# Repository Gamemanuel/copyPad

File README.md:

# copyPad
a macro pad for prgramers

# screenshot of overall hackpad

# A screenshot of my schematic

# A screenshot of my PCB

# BOM
* OLED screen
* encoder
* 4 headsetinserts
* 6 switches
* 6 Diodes
* 6 LEDS

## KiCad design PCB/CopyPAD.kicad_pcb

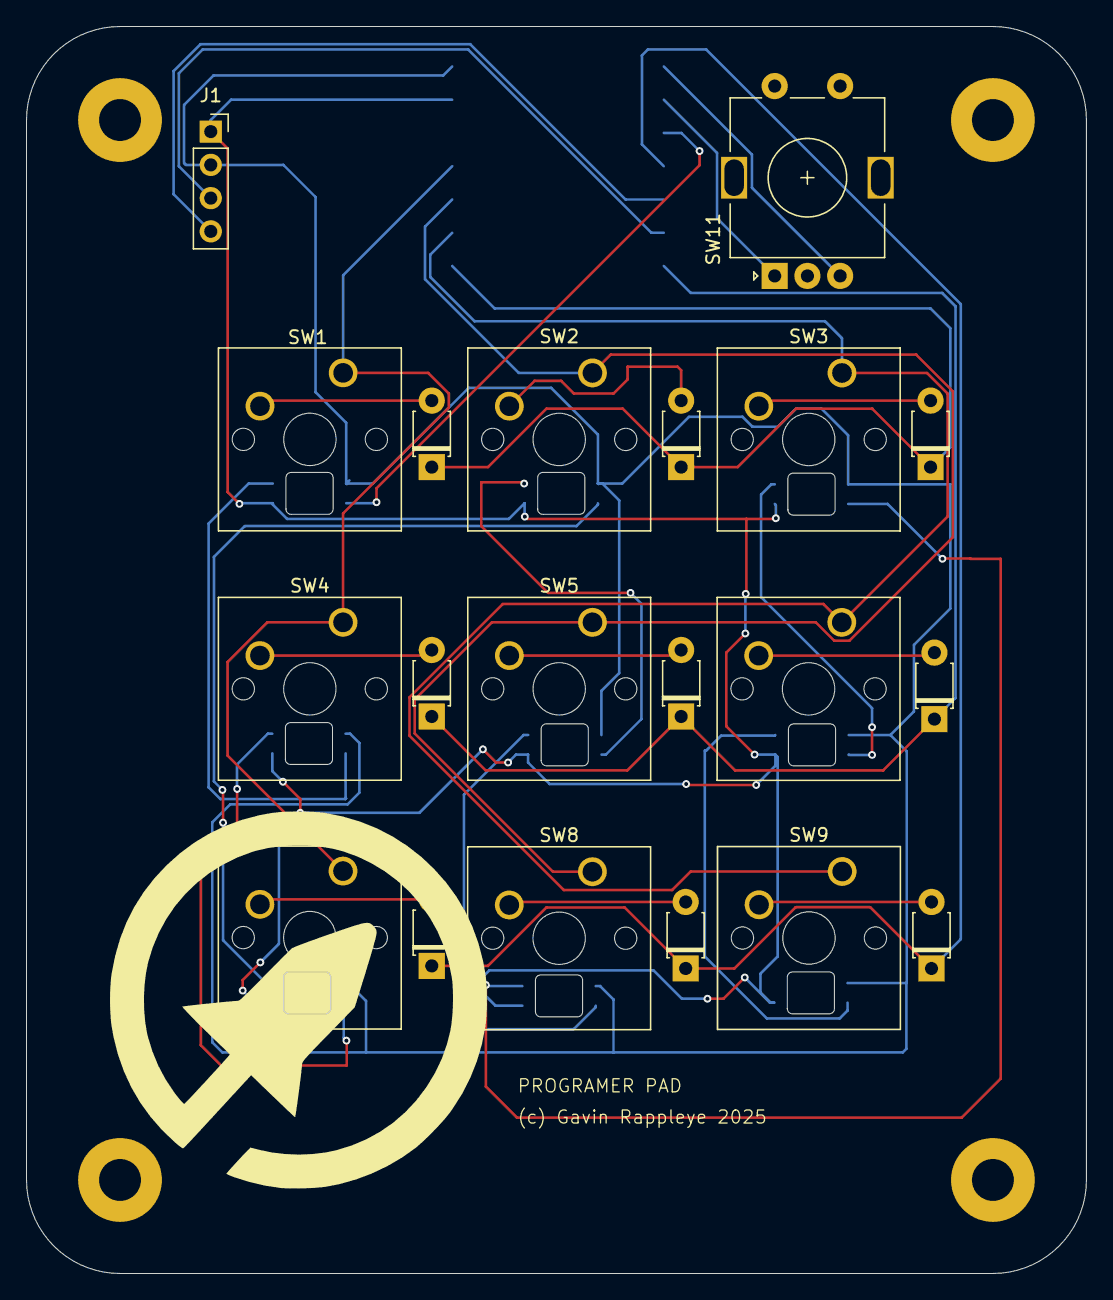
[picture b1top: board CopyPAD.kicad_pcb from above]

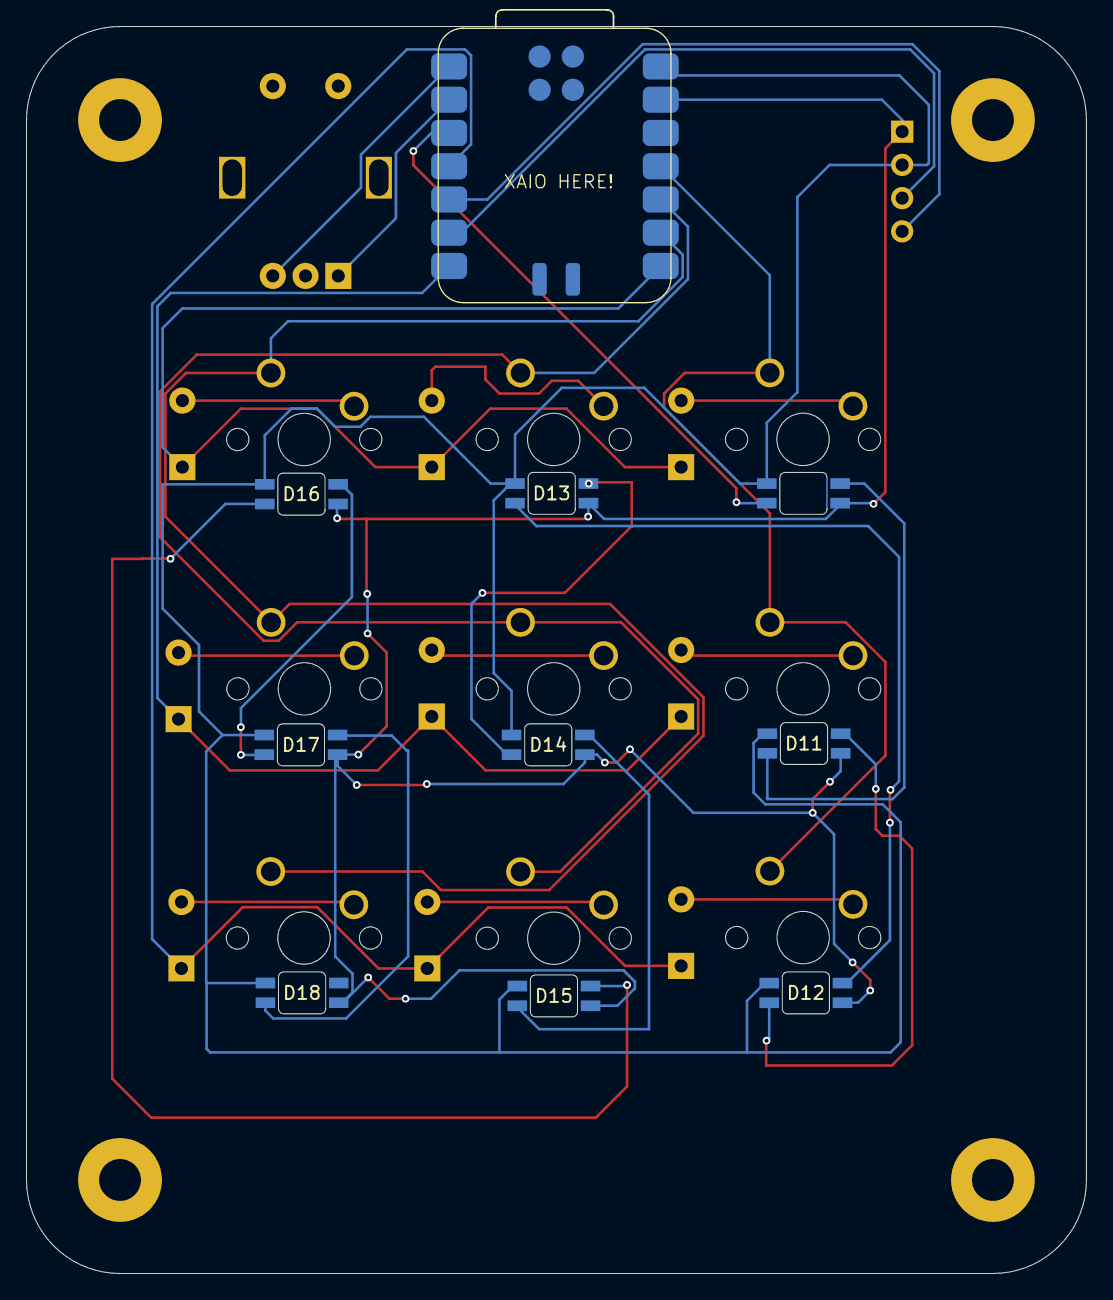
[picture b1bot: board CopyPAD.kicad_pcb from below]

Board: 2 copper layers, 81.0 x 95.2 mm, 34 parts (10 on the bottom side), 30 nets.

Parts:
D1, D11, D12, D13, D14, D15, D16, D17, D18: SK6812MINI; BAcklight
D2, D3, D4, D5, D6, D7, D8, D9, D10: D; D_T-1_P5.08mm_Horizontal
H1, H2, H3, H4: MountingHole; MountingHole_3.2mm_M3_Pad
J1: Conn_01x04_MountingPin; PinSocket_1x04_P2.54mm_Vertical
SW1, SW2, SW3, SW4, SW5, SW6, SW7, SW8, SW9: SW_Push_45deg; SW_Cherry_MX_1.00u_PCB
SW11: RotaryEncoder_Switch; RotaryEncoder_Alps_EC11E-Switch_Vertical_H20mm
U1: XIAO-RP2040-DIP; XIAO-RP2040-SMD

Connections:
+5V: D1.4 (VDD), D11.4 (VDD), D12.4 (VDD), D13.4 (VDD), D14.4 (VDD), D15.4 (VDD), D16.4 (VDD), D17.4 (VDD), D18.4 (VDD), J1.2, U1.14 (VBUS)
/SCL: J1.3, U1.6 (GPIO7/SCL)
/SDA: J1.4, U1.5 (GPIO6/SDA)
Column 0: SW1.1, SW4.1, SW7.1, U1.11 (GPIO3/MOSI)
Column 1: SW2.1, SW5.1, SW8.1, U1.10 (GPIO4/MISO)
Column 2: SW3.1, SW6.1, SW9.1, U1.9 (GPIO2/SCK)
GND: D1.2 (VSS), D11.2 (VSS), D12.2 (VSS), D13.2 (VSS), D14.2 (VSS), D15.2 (VSS), D16.2 (VSS), D17.2 (VSS), D18.2 (VSS), J1.1, U1.13 (GND)
unnamed: D1.3 (DIN), U1.3 (GPIO28/ADC2/A2)
unnamed: D1.1 (DOUT), D11.3 (DIN)
unnamed: D2.2 (A), SW1.2
unnamed: D3.2 (A), SW2.2
unnamed: D4.2 (A), SW3.2
unnamed: D5.2 (A), SW4.2
unnamed: D6.2 (A), SW5.2
unnamed: D7.2 (A), SW6.2
unnamed: D8.2 (A), SW7.2
unnamed: D9.2 (A), SW8.2
unnamed: D10.2 (A), SW9.2
unnamed: D11.1 (DOUT), D12.3 (DIN)
unnamed: D12.1 (DOUT), D13.3 (DIN)
unnamed: D13.1 (DOUT), D14.3 (DIN)
unnamed: D14.1 (DOUT), D15.3 (DIN)
unnamed: D15.1 (DOUT), D16.3 (DIN)
unnamed: D16.1 (DOUT), D17.3 (DIN)
unnamed: D17.1 (DOUT), D18.3 (DIN)
unnamed: SW11.B, U1.1 (GPIO26/ADC0/A0)
unnamed: SW11.A, U1.2 (GPIO27/ADC1/A1)
Row 0: D2.1 (K), D3.1 (K), D4.1 (K), U1.8 (GPIO1/RX)
Row 1: D5.1 (K), D6.1 (K), D7.1 (K), U1.7 (GPIO0/TX)
Row 2: D8.1 (K), D9.1 (K), D10.1 (K), U1.4 (GPIO29/ADC3/A3)

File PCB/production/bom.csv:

Designator,Footprint,Quantity,Value,LCSC Part #
"D1, D11, D12, D13, D14, D15, D16, D17, D18",BAcklight,9,SK6812MINI,
"D10, D2, D3, D4, D5, D6, D7, D8, D9",D_T-1_P5.08mm_Horizontal,9,D,
J1,PinSocket_1x04_P2.54mm_Vertical,1,Conn_01x04_MountingPin,
"SW1, SW2, SW3, SW4, SW5, SW6, SW7, SW8, SW9",SW_Cherry_MX_1.00u_PCB,9,SW_Push_45deg,
SW11,RotaryEncoder_Alps_EC11E-Switch_Vertical_H20mm,1,RotaryEncoder_Switch,
U1,XIAO-RP2040-SMD,1,XIAO-RP2040-DIP,

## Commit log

2025-07-02 let there be code
2025-07-02 fixed PCB voltadge error
2025-07-02 fixed issue with spacing
2025-07-04 removed top pad
